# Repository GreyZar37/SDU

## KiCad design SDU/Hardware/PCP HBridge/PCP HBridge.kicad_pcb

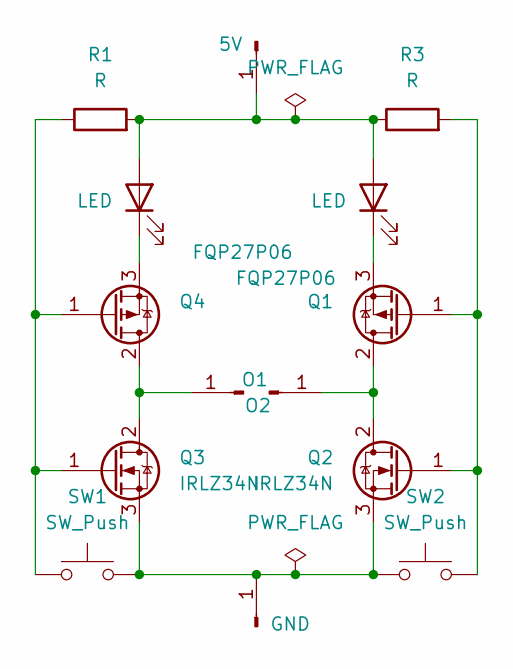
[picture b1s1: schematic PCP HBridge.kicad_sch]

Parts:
D1, D2: LED; LED_0201_0603Metric
J1: GND; PinHeader_1x01_P2.54mm_Vertical
J2: 5V; PinHeader_1x01_P2.54mm_Vertical
J3: O1; PinHeader_1x01_P2.54mm_Vertical
J4: O2; PinHeader_1x01_P2.54mm_Vertical
Q1, Q4: FQP27P06; TO-220-3_Vertical
Q2, Q3: IRLZ34N; TO-220-3_Vertical
R1, R3: R; R_0805_2012Metric
SW1, SW2: SW_Push; SW_SPST_B3S-1000

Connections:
unnamed: D1.2 (A), D2.2 (A), J2.1, R1.2, R3.1
unnamed: D1.1 (K), Q4.3 (S)
unnamed: D2.1 (K), Q1.3 (S)
unnamed: J1.1, Q2.3 (S), Q3.3 (S), SW1.2, SW2.1
unnamed: J3.1, Q3.2 (D), Q4.2 (D)
unnamed: J4.1, Q1.2 (D), Q2.2 (D)
unnamed: Q1.1 (G), Q2.1 (G), R3.2, SW2.2
unnamed: Q3.1 (G), Q4.1 (G), R1.1, SW1.1

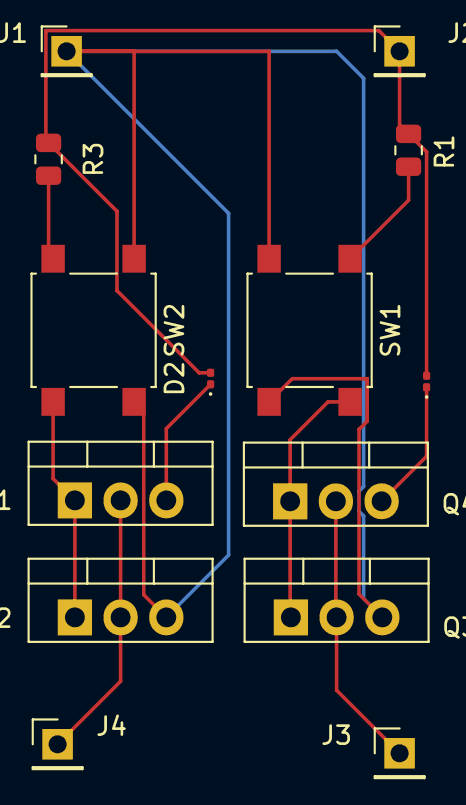
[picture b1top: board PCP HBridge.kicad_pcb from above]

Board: 2 copper layers, 14 parts (0 on the bottom side), 8 nets.

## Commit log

2024-09-03 Start
2024-09-05 Website Update
2024-09-05 Tilføjelse af basis CSS og ændring på Liste
    Basal css til headers og text, og listen er ændret således den er indentet på hvert punkt, det gamle kode er i kommentar under så det kan tages tilbage hvis det skulle ønskes
2024-09-05 Illeris fire læringstyper
2024-09-05 website
2024-09-05 Learningtypes
2024-09-05 Header
2024-09-05 New animation
2024-09-06 Classes and new CSS
2024-09-12 monke
2024-10-28 Code
2024-11-04 R and Web
2024-11-15 Deleted stationær verden
2024-11-20 Website Homepage
2024-11-20 Update web
2024-11-21 New build
2024-11-26 Project
2024-12-09 Hjemmeside
2024-12-09 Ai changes
2025-01-05 Statistik Eksamen
2025-01-27 Exam
2025-01-27 Materials
2025-05-30 Bridge
2025-10-20 Opgaver
2025-10-20 Data
2025-10-21 Python
2025-10-21 algo
2025-10-22 Algoritmer Færdig
2025-11-09 Journal
2025-11-24 SDU work
2025-12-05 school
2026-01-05 eksamn
2026-01-05 more eksam
